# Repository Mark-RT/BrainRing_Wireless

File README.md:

# BrainRing_Wireless

Разработка для игры BrainRing - беспроводная версия. Участников до 5. Для устройства ведущего есть прошивка `master`, а для всех участников одна прошивка `slave`.

## Яркость лент

Яркость лент игроков настраивается с пульта ведущего: **удерживайте кнопку 2 секунды** — яркость станет на 10% ниже. Держите дальше — каждую секунду ещё на 10%: 100% → 90% → … → 20% → снова 100%. Отпустите на нужной ступени. Каждая ступень сразу сохраняется в пульте ведущего, отдельно подтверждать не нужно. Чем ярче, тем выше сигнал, а ленты горят ровным светом, пока идёт настройка. Нажатие кнопки сразу сбрасывает раунд, поэтому меняйте яркость между вопросами. В «Саймоне» яркость меняется так же, но только в лобби.

## Игра «Саймон»

По умолчанию пульт ведущего всегда включается в брейн-ринг. Чтобы сыграть в «Саймона», **зажмите кнопку на пульте ведущего при включении и держите 3 секунды** (тики, светодиод разгорается фиолетовым, в конце мелодия). Для возврата в брейн-ринг выключите и включите пульт без кнопки.

Игра командная: каждый игрок отвечает за свой цвет. Пульты показывают последовательность, команда повторяет её по порядку, каждый жмёт свою кнопку, когда подходит его цвет. У команды 3 жизни. Команда — это пульты, которые были на связи в момент старта; она не меняется до конца игры. Пульт, включённый позже, тускло светит белым и не участвует.

Подробная инструкция: [docs/BrainRing_Wireless_Instruction.pdf](docs/BrainRing_Wireless_Instruction.pdf) (исходник — `docs/instruction/instruction.html`).

**Кнопка ведущего:**

| Когда | Действие | Результат |
|---|---|---|
| Лобби (фиолетовые вспышки = число игроков на связи) | клик | старт игры |
| Лобби | удержание 2 с (и дальше) | яркость лент −10% (и дальше каждую секунду) |
| Показ счёта или отсчёт перед раундом | клик | придержать игру; следующий клик — отсчёт заново |
| Ввод | клик | показать последовательность ещё раз (3 раза за игру, бонус раунда сгорает) |
| Идущая игра | удержание 2 с | закончить игру и показать счёт |
| Конец игры | клик | в лобби, новая игра |

**Что видно на лентах игроков:**

- **Перед раундом:** 2 с линейка очков (1 LED = 1 очко, каждый 5-й белый) и жизни (красные точки в конце ленты), затем отсчёт 3-2-1 со вспышками (по 1 с, последний сигнал выше и длиннее) и сразу первый цвет.
- **Ввод:** заполнение ленты показывает прогресс. За 2 с до конца времени на нажатие лента наливается красным (20% → 60%).
- **После раунда:** 1 с бегущие огни (или 1,5 с красный строб у виновника ошибки), затем 1 с паузы.
- **Ошибка или пропуск очереди:** лента виновника стробит красным, минус жизнь, последовательность показывается заново.
- **Янтарная пульсация:** кто-то пропал со связи, игра на паузе, жизнь не снимается.
- **Конец игры:** счёт набирается по одному LED с тиком на пульте ведущего.

Светодиод ведущего во время ввода показывает жизни: зелёный = 3, жёлтый = 2, красный = 1.

**Очки:** раунд +1, раунд без ошибок и повторов +1, особый раунд +1.

**Сложность:** цепочка растёт (с 6-го раунда иногда сразу на 2 шага), показ ускоряется, на нажатие остаётся меньше времени: 4,4 с в 1-м раунде, на 0,1 с меньше за раунд, но не меньше 2,5 с (с 20-го раунда). На первое нажатие в раунде — на 1 с больше. С 5-го раунда случаются «спурты» (показ ещё быстрее), с 9-го — «тихие раунды» (показ без нот); особый раунд объявляется стробом и трелью.

Устройства работают на принципе обратной связи, постоянной. То есть Игроки в любой момент времени, даже если была перезагрузка или потеря связи, знают, выиграли они или нет. Этот принцип конечно идёт в ущерб энергопотреблению, но в плюс стабильности работы, так как проверено временем.

По какой-то причине 1 версия перестала работать. Есть подозрение что обновилась библиотека и что-то пошло не так. Поэтому 2-я версия усовершенствованная (иногда были проблемы что игроки вместе нажимали на кнопку и ни у кого не сработало) и на всякий случай оставляю библиотеку которая точно работала на момент загрузки кода.

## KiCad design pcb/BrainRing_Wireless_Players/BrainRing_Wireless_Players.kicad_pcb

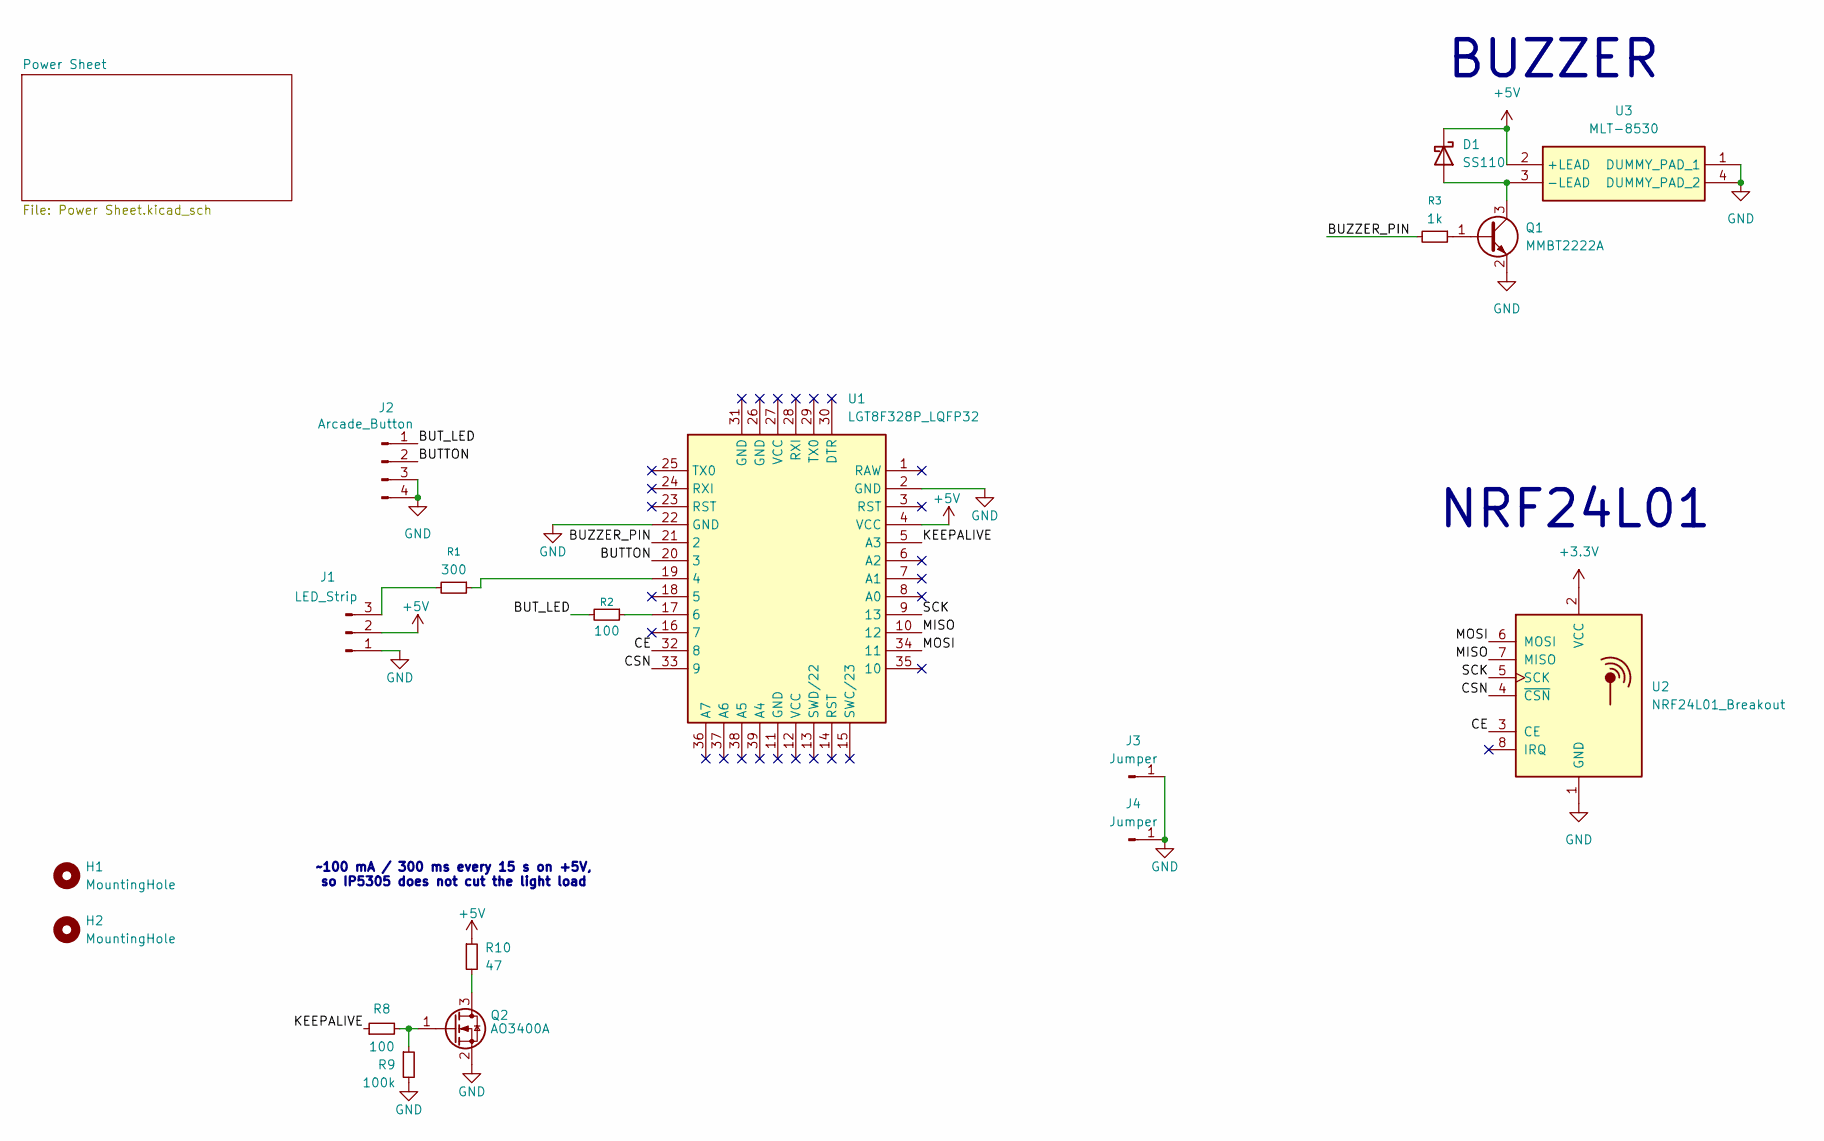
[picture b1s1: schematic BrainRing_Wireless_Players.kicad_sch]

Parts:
D1: SS110; D_SMA
H1, H2: MountingHole; MountingHole_2.2mm_M2
J1: LED_Strip; JST_EH_B3B-EH-A_1x03_P2.50mm_Vertical
J2: Arcade_Button; JST_EH_B4B-EH-A_1x04_P2.50mm_Vertical
J3, J4: Jumper; PinHeader_1x01_P2.54mm_Vertical
Q1: MMBT2222A; SOT-23
Q2: AO3400A; SOT-23
R1: 300; R_0603_1608Metric
R2, R8: 100; R_0603_1608Metric
R3: 1k; R_0603_1608Metric
R9: 100k; R_0603_1608Metric
R10: 47; R_1206_3216Metric
U1: LGT8F328P_LQFP32; Manufacturer Part New SchematicLib
U2: NRF24L01_Breakout; nRF24L01_Breakout
U3: MLT-8530; MLT8530; Manufacturer_Part_Number MLT-8530

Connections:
+3.3V: U2.2 (VCC); also elsewhere on the board
+5V: D1.1 (K), J1.2, R10.1, U1.4 (VCC), U3.2 (+LEAD); also elsewhere on the board
/BUTTON: J2.2, U1.20 (3)
/BUT_LED: J2.1, R2.2
/BUZZER_PIN: R3.2, U1.21 (2)
/CE: U1.32 (8), U2.3 (CE)
/CSN: U1.33 (9), U2.4 (~CSN)
/KEEPALIVE: R8.1, U1.5 (A3)
/MISO: U1.10 (12), U2.7 (MISO)
/MOSI: U1.34 (11), U2.6 (MOSI)
/SCK: U1.9 (13), U2.5 (SCK)
GND: J1.1, J2.3, J2.4, J3.1 (Pin_1_1), J4.1 (Pin_1_1), Q1.2 (E), Q2.2 (S), R9.2, U1.2 (GND), U1.22 (GND), U2.1 (GND), U3.1 (DUMMY_PAD_1), U3.4 (DUMMY_PAD_2); also elsewhere on the board
unnamed: D1.2 (A), Q1.3 (C), U3.3 (-LEAD)
unnamed: J1.3, R1.2
unnamed: Q1.1 (B), R3.1
unnamed: Q2.3 (D), R10.2
unnamed: Q2.1 (G), R8.2, R9.1
unnamed: R1.1, U1.19 (4)
unnamed: R2.1, U1.17 (6)

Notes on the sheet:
~100 mA / 300 ms every 15 s on +5V, so IP5305 does not cut the light load
NRF24L01
BUZZER

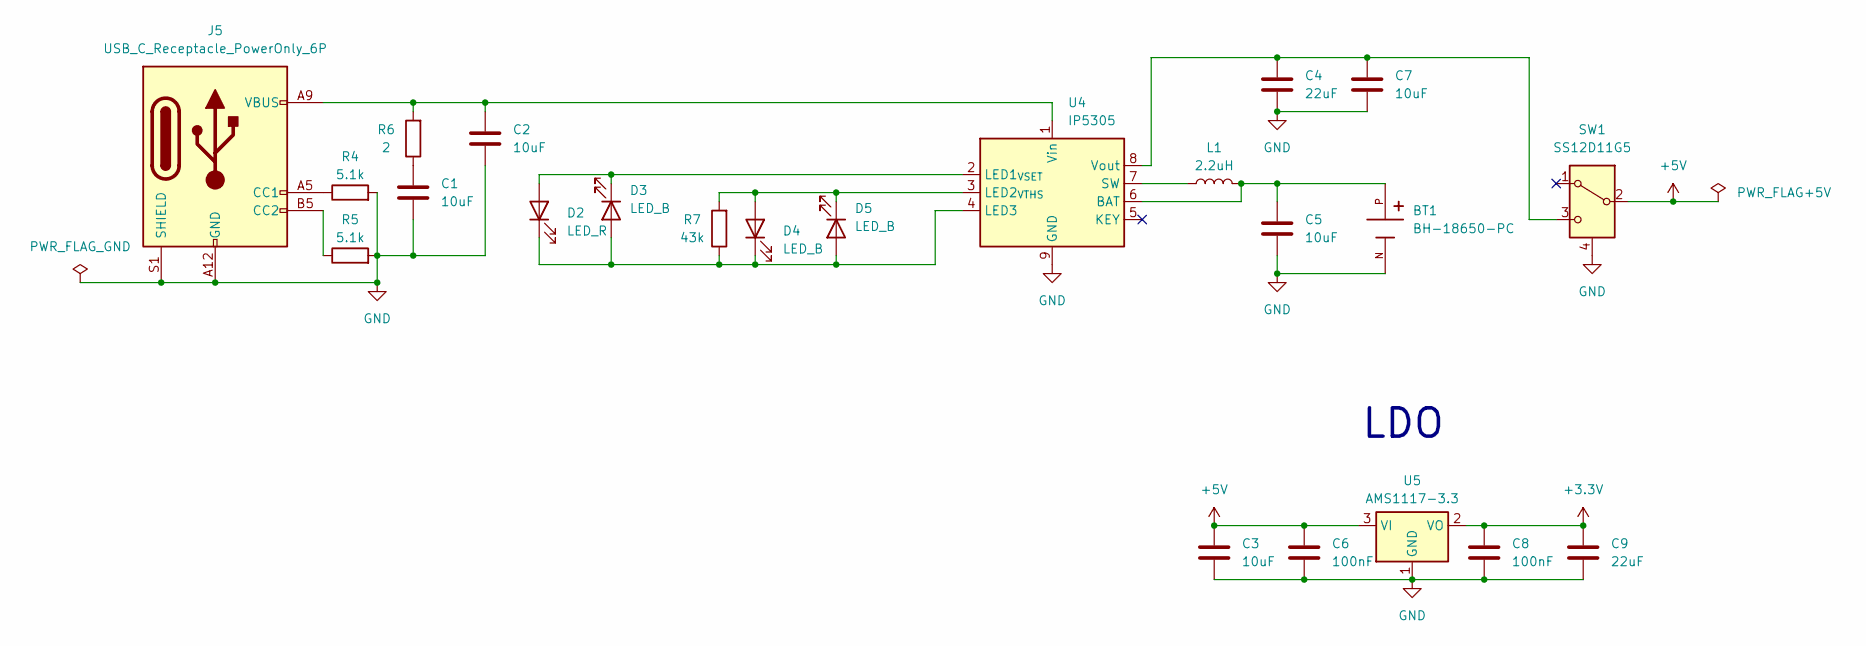
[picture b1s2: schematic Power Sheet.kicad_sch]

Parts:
BT1: BH-18650-PC; BAT_BH-18650-PC
C1, C2, C3, C5, C7: 10uF; C_0805_2012Metric_Pad1.18x1.45mm_HandSolder
C4, C9: 22uF; C_0805_2012Metric_Pad1.18x1.45mm_HandSolder
C6, C8: 100nF; C_0805_2012Metric_Pad1.18x1.45mm_HandSolder
D2: LED_R; LED_0805_2012Metric
D3, D4, D5: LED_B; LED_0805_2012Metric
J5: USB_C_Receptacle_PowerOnly_6P; USB_C_Receptacle_HRO_TYPE-C-31-M-17
L1: 2.2uH; L_APV_APH0630
R4, R5: 5.1k; R_0603_1608Metric_Pad0.98x0.95mm_HandSolder
R6: 2; R_0603_1608Metric_Pad0.98x0.95mm_HandSolder
R7: 43k; R_0603_1608Metric_Pad0.98x0.95mm_HandSolder
SW1: SS12D11G5
U4: IP5305; HSOP-8-1EP_3.9x4.9mm_P1.27mm_EP2.41x3.1mm
U5: AMS1117-3.3; SOT-223-3_TabPin2

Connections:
+3.3V: C8.1, C9.1, U5.2 (VO); also elsewhere on the board
+5V: C3.1, C6.1, SW1.2 (B), U5.3 (VI); also elsewhere on the board
GND: BT1.N, C1.2, C2.2, C3.2, C4.2, C5.2, C6.2, C7.2, C8.2, C9.2, J5.A12 (GND), J5.B12 (GND), J5.S1 (SHIELD), R4.2, R5.2, SW1.4 (Shield), U4.9 (GND), U5.1 (GND); also elsewhere on the board
unnamed: C1.1, R6.1
unnamed: D2.2 (A), D3.1 (K), U4.2 (LED1_{VSET})
unnamed: D2.1 (K), D3.2 (A), D4.1 (K), D5.2 (A), R7.1, U4.4 (LED3)
unnamed: D4.2 (A), D5.1 (K), R7.2, U4.3 (LED2_{VTHS})
unnamed: J5.A5 (CC1), R4.1
unnamed: J5.B5 (CC2), R5.1
unnamed: C4.1, C7.1, SW1.3 (C), U4.8 (Vout)
unnamed: BT1.P, C5.1, L1.2, U4.6 (BAT)
unnamed: L1.1, U4.7 (SW)
unnamed: C2.1, J5.A9 (VBUS), J5.B9 (VBUS), R6.2, U4.1 (Vin)

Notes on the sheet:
LDO

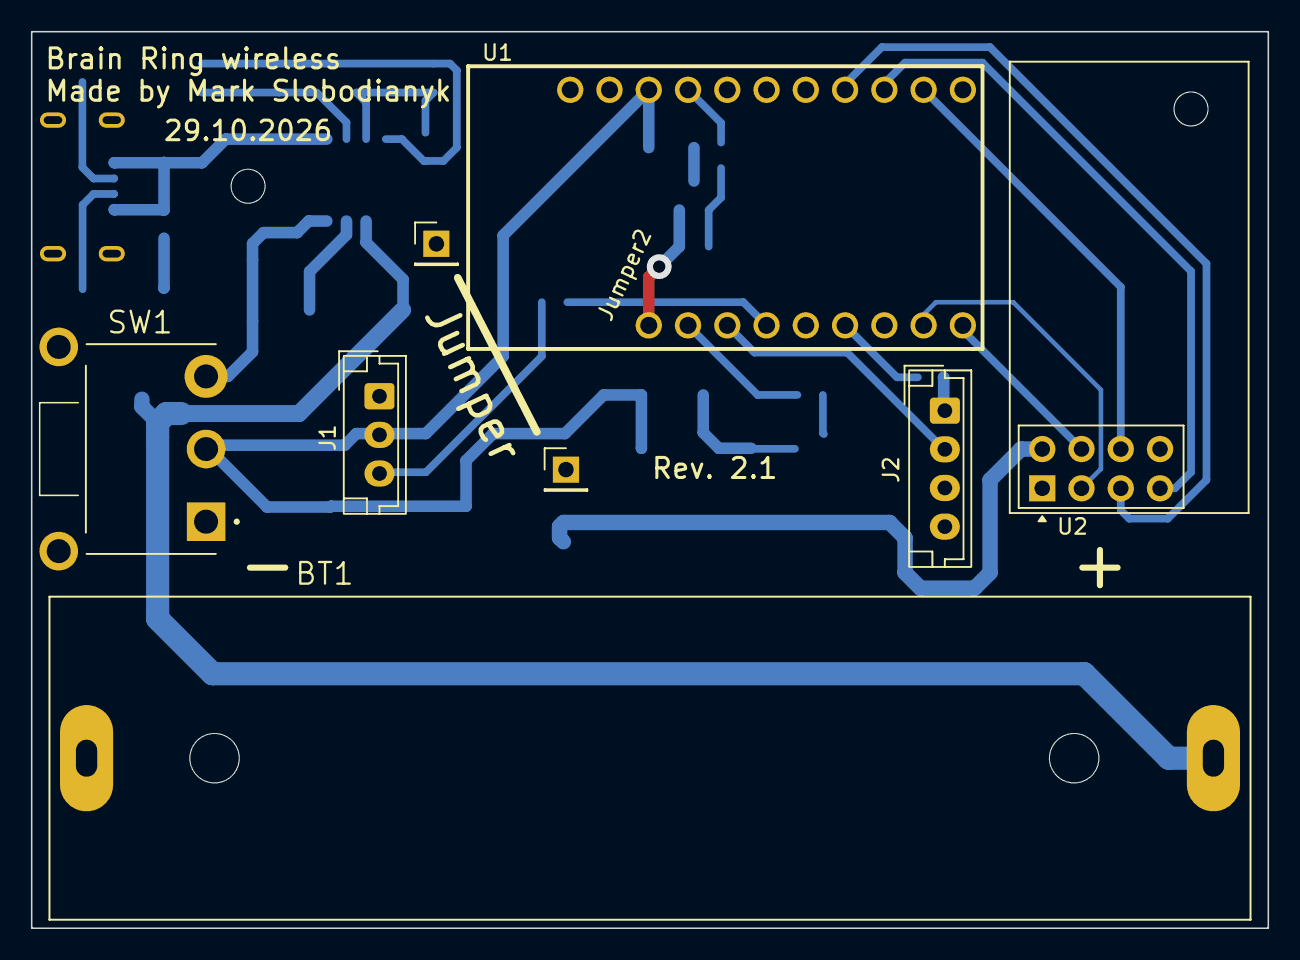
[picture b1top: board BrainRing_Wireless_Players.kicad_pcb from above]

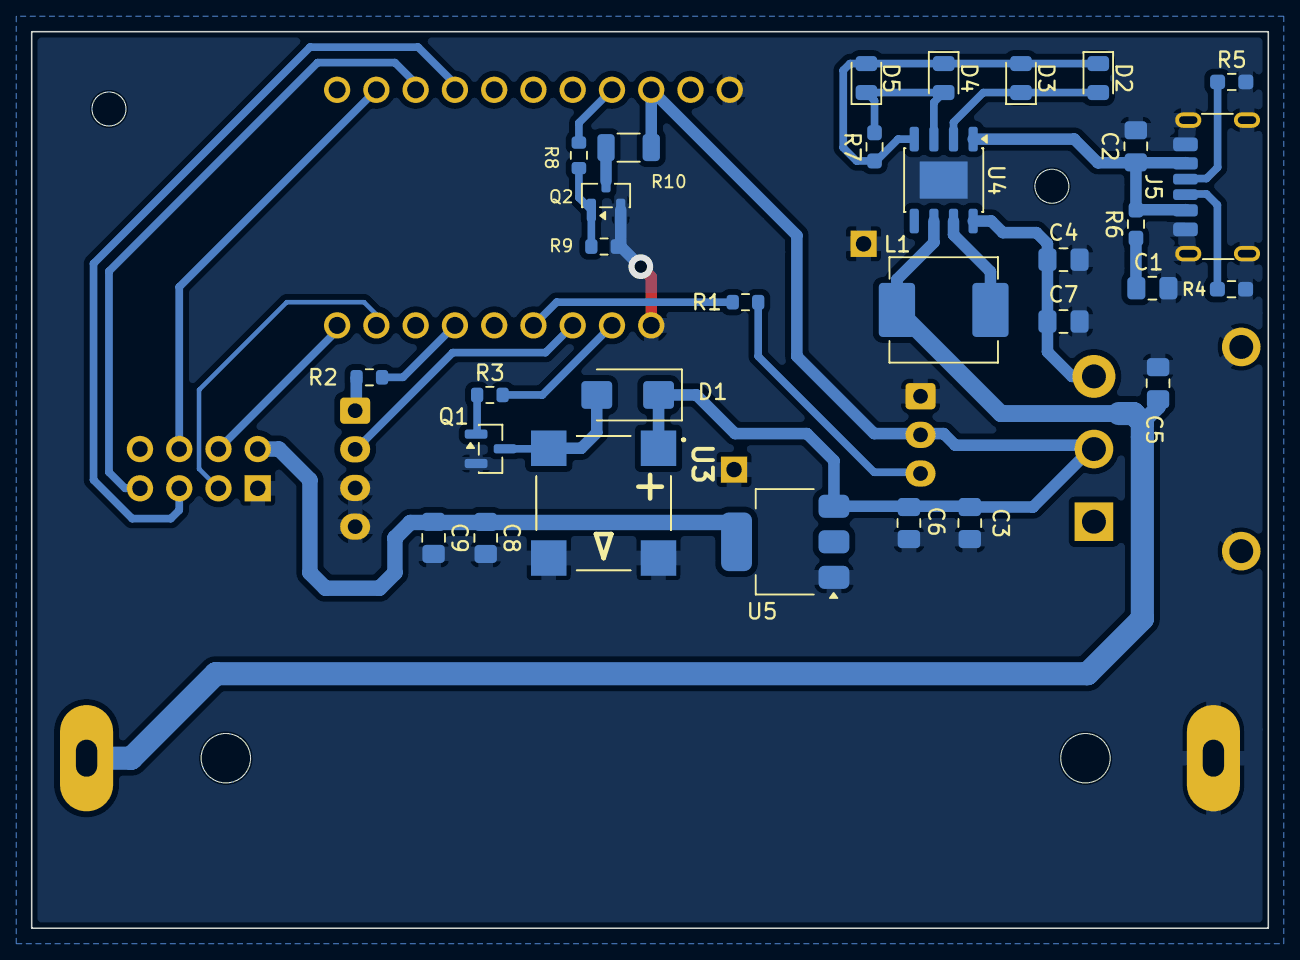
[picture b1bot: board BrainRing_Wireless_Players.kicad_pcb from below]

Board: 2 copper layers, 80.0 x 58.0 mm, 41 parts (32 on the bottom side), 29 nets.

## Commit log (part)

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2023-11-03 BrainRing_Wireless
2023-11-07 update main
2023-11-27 update code
2023-11-27 update sketchs
2025-04-30 update all
2026-03-17 add kicad
2026-03-17 upd sch
2026-03-18 add pcb2
2026-04-23 upd2.0
2026-04-23 GOOD. its working
2026-06-05 change box and cap
